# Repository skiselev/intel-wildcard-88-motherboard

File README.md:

# Intel Wildcard 88 Motherboard
An IBM PC/XT compatible motherboard utilizing the [Intel Wildcard 88](documentation/Wildcard%2088%20Datasheet.pdf) module

## Intel Wildcard 88
The Intel Wildcard 88 module was announced by Intel in August 1988. In early 1990's Intel sold Wildcard 88 line to the Canadian [Megatel Computer Corporation](https://web.archive.org/web/20060613014211/http://www.megatel.com/). Here is their [Wildcard 88 page](https://web.archive.org/web/20060615183926/http://megatel.com/html/embedded/control/ov_cwm.htm).

### Specifications of Wildcard 88 module
* The size is about 2" x 4" (50.8mm x 101.6mm)
* Intel 80C88A CPU - 4.77 MHz, 7.15 MHz turbo mode, and 9.54 MHz (Wildcard-88-10N only)
* Custom ASIC implementing functionality of most 82xx ICs (8259 PIC, 8254 PIT, 8237 DMA, 8255 PPI, 8284 clock generator, 8288 bus controller) and glue logic found on an XT motherboard. The ASIC seems actually be the [Faraday FE2010 or FE2010A (for Wildcard-88-10N)](https://github.com/skiselev/micro_8088/blob/master/Documentation/Faraday-XT_Controller-FE2010A.md) chipset
* Half a dozen of 74ALS244 buffers, 74ALS245 transceivers, and 74ALS373 latches to buffer the signals going out of the module.
* Socket for the ROM BIOS. 8 KiB (2764 type), 16 KiB (27C128 type), and 32 KiB (27C256 type) EPROMs are supported.
* Socket for the Intel 8087 floating point co-processor (FPU). Available on the 'N' models only.
* 68-pin SIMM edge connector to connect to the system board. The connector contains all signals found on an XT bus (8-bit ISA), signals required to interface to DRAM (CAS, RAS0 - RAS2, /DRAM, MUX), signals for XT keyboard, speaker output, external reset and video configuration inputs (on 'N' models only)

The Intel Wildcard 88 module was used in several XT compatible computers, for example in the [Leading Edge Model D](https://en.wikipedia.org/wiki/Leading_Edge_Model_D) computers (made by Daewoo). One of more unusual applications - it was used as a control module for the [Nikon NASA F4](https://en.wikipedia.org/wiki/Nikon_NASA_F4) camera, one of the first digital cameras that flew on several Space Shuttle missions.

## The Motherboard

### Overview
Most of the XT computer functionality is implemented on the Wildcard 88 module. The motherboard adds memory, ISA slots, and AT2XT keyboard converter, so that the motherboard can be used with a more modern PS/2 keyboard. It is designed to be as small as possible - the board size is 4.6" x 6.5", but yet functional enough to be used as a generic XT motherboard.

### Specifications
Here are motherboard specifications and ideas behind them:

* 5 ISA slots. Number of slots it tradeoff between board size and extensibility. 5 slots should be enough (the same number as on the original IBM PC motherboard), assuming the slots will be used for the following cards:
  1. Display card
  2. Floppy disk controller card
  3. Hard drive controller card, e.g. XT-IDE or XT-CF-Lite
  4. Audio card
  5. Available for other extension cards (e.g. network).
* The system memory is implemented using single 1 MiB (1 Mbit x 8) SIMM-30 module. The motherboard memory support circuit includes three 74F157 multiplexers, that are used to generate DRAM row / column addresses, a 74F245 buffer for the data bus, and a 74F27 NOR gate used to generate a single /RAS signal from RAS0 - RAS2 signals supplied by the Wildcard 88, and to invert CAS signal. Two otherwise available multiplexers are used to buffer and delay /MEMW signal to memory.
* The motherboard provides PS/2 compatible Mini-DIN keyboard connector.
   * The Wildcard 88 module provides an XT compatible keyboard interface.
   * The motherboard includes an AT2XT keyboard converter, implemented using a PIC12F629 microcontroller.
* Power supply: Motherboard is powered using a 8-pin connector, with 5V, 12V, and -12V voltages. Motherboard includes an LM7905 power regulator is used to convert -12V to -5V. Four diagnostic LEDs are provided on the motherboard to indicate voltage on each power rail. An additional 5V connector on the motherboard can be used to connect power to 3.5" floppy drive.
* The motherboard includes a 12 mm speaker, and a header for connecting an external speaker.
* Jumpers, switches, and connectors:
  * Reset switch - a 6 mm tactile button
  * P5 - Reset header for an external reset switch
  * P6 - Power LED
  * JP1 - VID0 - Video configuration jumper (mono / color)
  * JP2 - AT2XT keyboard converter configuration. Currently, if installed, the jumper configures firmware to pass 0xE0 scan code to the system. This is useful for international keyboards.

### Schematic and PCB Layout

* [Schematic - Version 1.0](KiCad/Wildcard%2088%20Motherboard%20-%20Schematic%20-%201.0.pdf)
* [PCB Layout - Version 1.0](KiCad/Wildcard%2088%20Motherboard%20-%20Board%20-%201.0.pdf)
* [KiCad design files](KiCad/)

### Bill of Materials

* [Wildcard 88 Motherboard project on Mouser](https://www.mouser.com/Tools/Project/Share?AccessID=80f9c13de3): Order most of the components
* [Wildcard 88 Motherboard project on OSHPark](https://oshpark.com/shared_projects/J2usAv54): Order the Wildcard 88 Motherboard PCB

Component type     | Reference | Description                                   | Quantity | Possible sources and notes 
------------------ | --------- | --------------------------------------------- | -------- | --------------------------
PCB                |           | Wildcard 88 Motherboard PCB                   | 1        | Order from a PCB manufacturer of your choice using provided [Gerber](gerber/) or [KiCad](KiCad/WildcardXT.kicad_pcb) files.
Connector          | BUS1 - BUS5 | 62 pin card edge connector, ISA             | 5        | Mouser [571-6-5530843-5](https://www.mouser.com/ProductDetail/571-6-5530843-5), [571-7-5530843-0](https://www.mouser.com/ProductDetail/571-7-5530843-0), [571-5645235-1](https://www.mouser.com/ProductDetail/571-5645235-1)
Capacitor          | C1 - C9   | 0.1uF ceramic capacitor, 5.08 mm lead spacing | 9        | Mouser [810-FG28X7R1H104KNT6](https://www.mouser.com/ProductDetail/810-FG28X7R1H104KNT6)
Capacitor          | C10       | 0.01uF ceramic capacitor, 5.08 mm lead spacing | 1       | Mouser [810-FG28X7R1H103KNT6](https://www.mouser.com/ProductDetail/810-FG28X7R1H103KNT6)
Capacitor          | C11 - C27 | 10uF ceramic or tantalum capacitor, 5.08 mm lead spacing | 17| Mouser [810-FG28X5R1E106MR06](https://www.mouser.com/ProductDetail/810-FG28X5R1E106MR06)
Diode              | D1        | 1N4148                                        | 1        | Mouser [512-1N4148TA](https://www.mouser.com/ProductDetail/512-1N4148TA), [512-1N4148](https://www.mouser.com/ProductDetail/512-1N4148)
LED                | D2-D5     | 3 mm LED, various colors                      | 4        | Mouser [593-VAOL-3LAE2](https://www.mouser.com/ProductDetail/593-VAOL-3LAE2) (Red), [593-VAOL-3GCE4](https://www.mouser.com/ProductDetail/593-VAOL-3GCE4) (Yellow), [593-VAOL-3MDE2](https://www.mouser.com/ProductDetail/593-VAOL-3MDE2) (Green), [593-VAOL-3LSBY2](https://www.mouser.com/ProductDetail/593-VAOL-3LSBY2) (Blue)
Pin Header         | JP1, JP2, P5, P6 | 1x2 pin header                         | 4        | Mouser [649-68002-102HLF](https://www.mouser.com/ProductDetail/649-68002-102HLF)
Connector          | P1        | 8 pin connector with friction lock            | 1        | Mouser [571-6404568](https://www.mouser.com/ProductDetail/571-6404568)
Connector          | P2        | 6 pin Mini DIN connector                      | 1        | Mouser [806-KMDGX-6S-BS](https://www.mouser.com/ProductDetail/806-KMDGX-6S-BS)
Pin Header         | P3        | 1x4 pin header                                | 1        | Mouser [649-68002-204HLF](https://www.mouser.com/ProductDetail/649-68002-204HLF)
Connector          | P4        | 2 pin connector with friction lock            | 1        | Mouser [571-6404562](https://www.mouser.com/ProductDetail/571-6404562)
Transistor         | Q1        | PN2222A                                       | 1        | Mouser [512-PN2222ATA](https://www.mouser.com/ProductDetail/512-PN2222ATA)
Resistor           | R1        | 1k resistor                                   | 1        | Mouser [603-MFR-25FRF521K](https://www.mouser.com/ProductDetail/603-MFR-25FRF521K)
Resistor           | R2 - R4   | 470 ohm resistor                              | 3        | Mouser [603-MFR-25FRF52-470R](https://www.mouser.com/ProductDetail/603-MFR-25FRF52-470R)
Resistor           | R4, R5    | 1.5k resistor                                 | 2        | Mouser [603-MFR-25FRF521K5](https://www.mouser.com/ProductDetail/603-MFR-25FRF521K5)
Resistor Array     | RR1, RR2  | 33 ohm resistor array, DIP-14                 | 2        | Mouser [652-4114R-1LF-33](https://www.mouser.com/ProductDetail/652-4114R-1LF-33), or use 14 discrete resistors [603-MFR-25FRF52-33R](https://www.mouser.com/ProductDetail/603-MFR-25FRF52-33R)
Resistor Array     | RR3, RR4  | 4.7k resistor array, SIP-9                    | 2        | Mouser [652-4609X-1LF-4.7K](https://www.mouser.com/ProductDetail/652-4609X-1LF-4.7K), [858-L091S472LF](https://www.mouser.com/ProductDetail/858-L091S472LF), [652-4309R-1LF-4.7K](https://www.mouser.com/ProductDetail/652-4309R-1LF-4.7K)
Speaker            | SP1       | 12 mm speaker                                 | 1        | Mouser [665-AT-1224TWTR](https://www.mouser.com/ProductDetail/665-AT-1224TWTR)
Button             | SW1       | 6 mm tactile button                           | 1        | Mouser [653-B3F-1000](https://www.mouser.com/ProductDetail/653-B3F-1000)
Module             | U1        | Intel Wildcard 88 Module                      | 1        | eBay
Module             | U2        | SIMM-30 RAM, 1 Mbit x 8                       | 1        | eBay
Integrated Circuit | U3        | PIC12C629                                     | 1        | Mouser [579-PIC12F629IP](https://www.mouser.com/ProductDetail/579-PIC12F629IP), [579-PIC12F629-E/P](https://www.mouser.com/ProductDetail/579-PIC12F629-E-P)
Integrated Circuit | U4        | 74ALS245                                      | 1        | Mouser [595-SN74F245N](https://www.mouser.com/ProductDetail/595-SN74F245N), [595-SN74F245NE4](https://www.mouser.com/ProductDetail/595-SN74F245NE4) [595-SN74ALS245AN](https://www.mouser.com/ProductDetail/595-SN74ALS245AN), [595-SN74ACT245N](https://www.mouser.com/ProductDetail/595-SN74ACT245N), [595-CD74ACT245E](https://www.mouser.com/ProductDetail/595-CD74ACT245E)
Integrated Circuit | U5 - U7   | 74ALS158                                      | 3        | Mouser [595-SN74F157AN](https://www.mouser.com/ProductDetail/595-SN74F157AN), [595-SN74ALS157AN](https://www.mouser.com/ProductDetail/595-SN74ALS157AN), [595-CD74ACT157E](https://www.mouser.com/ProductDetail/595-CD74ACT157E)
Integrated Circuit | U8        | 74ALS27                                       | 1        | Mouser [595-SN74F27N](https://www.mouser.com/ProductDetail/595-SN74F27N), [595-SN74ALS27AN](https://www.mouser.com/ProductDetail/595-SN74ALS27AN)
Integrated Circuit | U9        | LM7905                                        | 1        | Mouser [863-MC7905CTG](https://www.mouser.com/ProductDetail/863-MC7905CTG)
Socket             | U1        | 68 pin SIMM socket, vertical                  | 1        | Make from a 72 pin socket Mouser [571-5822021-4](https://www.mouser.com/ProductDetail/571-5822021-4)
Socket             | U2        | 30 pin SIMM socket, vertical                  | 1        | eBay
Socket             | U3        | 8 pin DIP socket                              | 1        | Mouser [517-4808-3000-CP](https://www.mouser.com/ProductDetail/517-4808-3000-CP)
Socket             | U4        | 20 pin DIP socket                             | 1        | Mouser [517-4820-3000-CP](https://www.mouser.com/ProductDetail/517-4820-3000-CP)
Socket             | U5 - U7   | 16 pin DIP socket                             | 3        | Mouser [517-4816-3000-CP](https://www.mouser.com/ProductDetail/517-4816-3000-CP)
Socket             | U8        | 14 pin DIP socket                             | 1        | Mouser [517-4814-3000-CP](https://www.mouser.com/ProductDetail/517-4814-3000-CP)

## Software

### BIOS

The BIOS binary files from The Leading Edge - Model D are provided in the [software](software/) directory of this repository.

Since the Wildcard 88 module uses [Faraday FE2010 or FE1020A chipsets](https://github.com/skiselev/micro_8088/blob/master/Documentation/Faraday-XT_Controller-FE2010A.md), the [8088 BIOS](https://github.com/skiselev/8088_bios) configured for these chipsets (e.g., Micro 8088 configuration) can be used instead. Note that the Wildcard 88 module uses an EPROM instead of a Flash ROM, therefore the BIOS configuration utility will not work. The BIOS configuration needs to be edited prior to programming the EPROM.

### AT2XT Firmware

The Wildcard 88 Motherboard integrates an AT2XT keyboard converter, implemented using PIC12F629 (U3). The firmware for this microcontroller is availabe from the [minuszerodegrees.net](http://minuszerodegrees.net/at2xtkb/XTATKEY_094.zip) and the [Vintage Computer Federation AT2XT page](https://forum.vcfed.org/index.php?threads/at2xt-keyboard-converter.26861/page-4#post-1242916). The HEX file with the firmware can be extracted from XTATKEY_094.zip.

## Red Tape

### Licensing

Intel Wildcard 88 Motherboard is an open source hardware project. The hardware design itself, including schematic and PCB layout design files are licensed under the strongly-reciprocal variant of [CERN Open Hardware Licence version 2](license-cern_ohl_s_v2.txt). Documentation, including this file, is licensed under the [Creative Commons Attribution-ShareAlike 4.0 International License](license-cc-by-sa-4.0.txt).

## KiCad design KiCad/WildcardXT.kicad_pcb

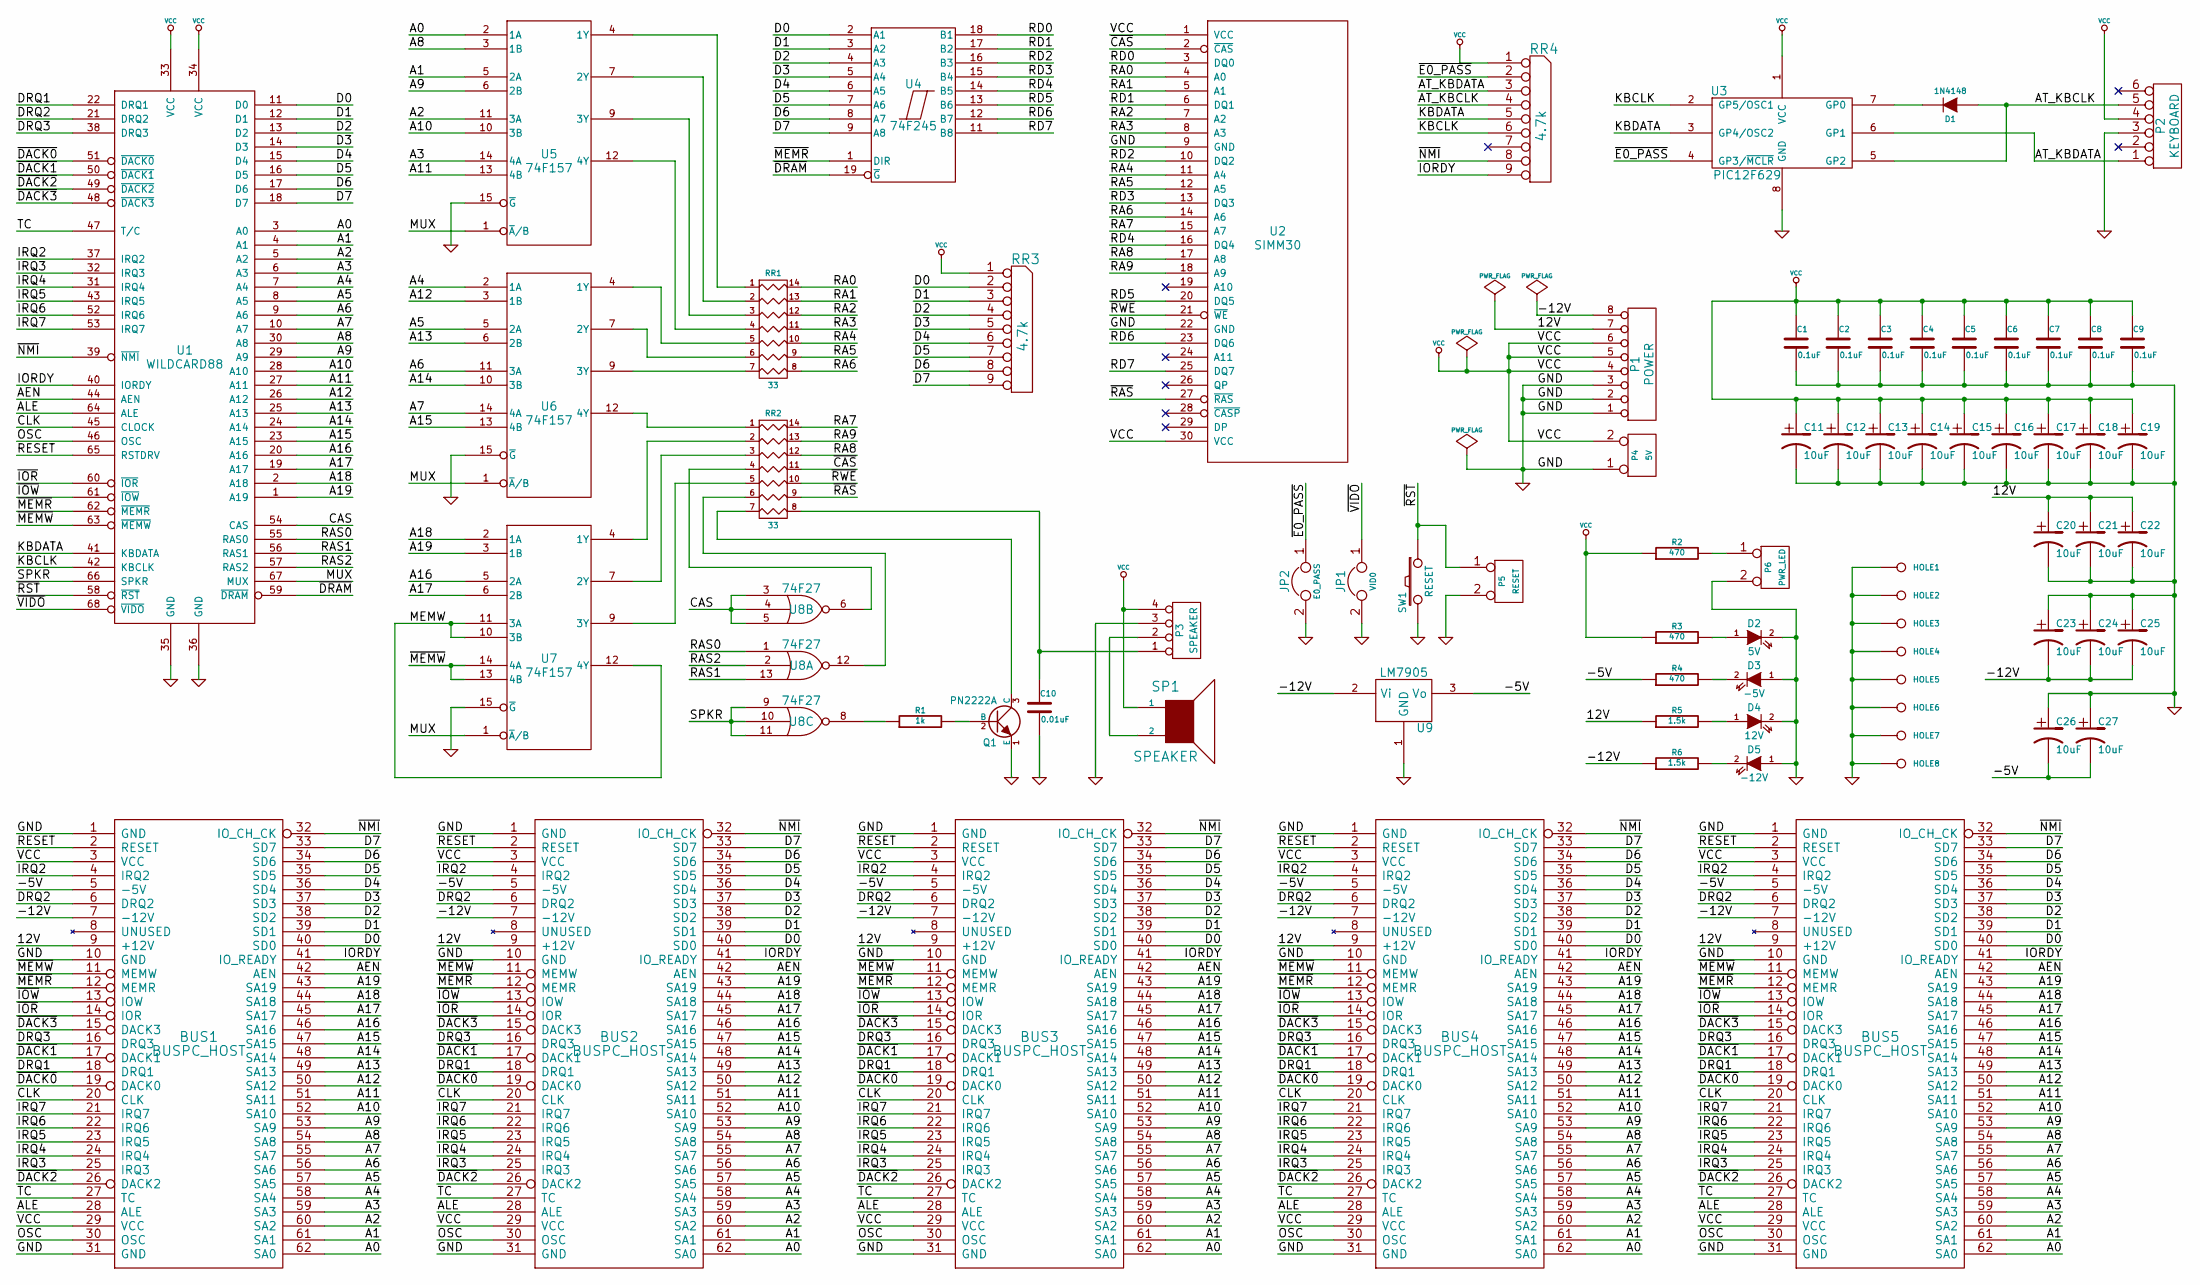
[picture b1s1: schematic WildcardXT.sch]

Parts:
BUS1, BUS2, BUS3, BUS4, BUS5: BUSPC_HOST
C1, C2, C3, C4, C5, C6, C7, C8, C9: 0.1uF
C10: 0.01uF
C11, C12, C13, C14, C15, C16, C17, C18, C19, C20, C21, C22, C23, C24, C25, C26, C27: 10uF
D1: 1N4148
D2: 5V
D3: -5V
D4: 12V
D5: -12V
HOLE1, HOLE2, HOLE3, HOLE4, HOLE5, HOLE6, HOLE7, HOLE8: CONN_1
JP1: VID0
JP2: E0_PASS
P1: POWER
P2: KEYBOARD
P3: SPEAKER
P4: 5V
P5: RESET
P6: PWR_LED
Q1: PN2222A
R1: 1k
R2, R3, R4: 470
R5, R6: 1.5k
RR1, RR2: 33
RR3, RR4: 4.7k
SP1: SPEAKER
SW1: RESET
U1: WILDCARD88
U2: SIMM30
U3: PIC12F629
U4: 74F245
U5, U6, U7: 74F157
U8: 74F27
U9: LM7905

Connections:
/12V: BUS1.9 (+12V), BUS2.9 (+12V), BUS3.9 (+12V), BUS4.9 (+12V), BUS5.9 (+12V), C20.1, C21.1, C22.1, P1.7, R5.1
/-5V: BUS1.5 (-5V), BUS2.5 (-5V), BUS3.5 (-5V), BUS4.5 (-5V), BUS5.5 (-5V), C26.2, C27.2, R4.1, U9.3 (Vo)
/-12V: BUS1.7 (-12V), BUS2.7 (-12V), BUS3.7 (-12V), BUS4.7 (-12V), BUS5.7 (-12V), C23.2, C24.2, C25.2, P1.8, R6.1, U9.2 (Vi)
/A0: BUS1.62 (SA0), BUS2.62 (SA0), BUS3.62 (SA0), BUS4.62 (SA0), BUS5.62 (SA0), U1.3 (A0), U5.2 (1A)
/A1: BUS1.61 (SA1), BUS2.61 (SA1), BUS3.61 (SA1), BUS4.61 (SA1), BUS5.61 (SA1), U1.4 (A1), U5.5 (2A)
/A2: BUS1.60 (SA2), BUS2.60 (SA2), BUS3.60 (SA2), BUS4.60 (SA2), BUS5.60 (SA2), U1.5 (A2), U5.11 (3A)
/A3: BUS1.59 (SA3), BUS2.59 (SA3), BUS3.59 (SA3), BUS4.59 (SA3), BUS5.59 (SA3), U1.6 (A3), U5.14 (4A)
/A4: BUS1.58 (SA4), BUS2.58 (SA4), BUS3.58 (SA4), BUS4.58 (SA4), BUS5.58 (SA4), U1.7 (A4), U6.2 (1A)
/A5: BUS1.57 (SA5), BUS2.57 (SA5), BUS3.57 (SA5), BUS4.57 (SA5), BUS5.57 (SA5), U1.8 (A5), U6.5 (2A)
/A6: BUS1.56 (SA6), BUS2.56 (SA6), BUS3.56 (SA6), BUS4.56 (SA6), BUS5.56 (SA6), U1.9 (A6), U6.11 (3A)
/A7: BUS1.55 (SA7), BUS2.55 (SA7), BUS3.55 (SA7), BUS4.55 (SA7), BUS5.55 (SA7), U1.10 (A7), U6.14 (4A)
/A8: BUS1.54 (SA8), BUS2.54 (SA8), BUS3.54 (SA8), BUS4.54 (SA8), BUS5.54 (SA8), U1.30 (A8), U5.3 (1B)
/A9: BUS1.53 (SA9), BUS2.53 (SA9), BUS3.53 (SA9), BUS4.53 (SA9), BUS5.53 (SA9), U1.29 (A9), U5.6 (2B)
/A10: BUS1.52 (SA10), BUS2.52 (SA10), BUS3.52 (SA10), BUS4.52 (SA10), BUS5.52 (SA10), U1.28 (A10), U5.10 (3B)
/A11: BUS1.51 (SA11), BUS2.51 (SA11), BUS3.51 (SA11), BUS4.51 (SA11), BUS5.51 (SA11), U1.27 (A11), U5.13 (4B)
/A12: BUS1.50 (SA12), BUS2.50 (SA12), BUS3.50 (SA12), BUS4.50 (SA12), BUS5.50 (SA12), U1.26 (A12), U6.3 (1B)
/A13: BUS1.49 (SA13), BUS2.49 (SA13), BUS3.49 (SA13), BUS4.49 (SA13), BUS5.49 (SA13), U1.25 (A13), U6.6 (2B)
/A14: BUS1.48 (SA14), BUS2.48 (SA14), BUS3.48 (SA14), BUS4.48 (SA14), BUS5.48 (SA14), U1.24 (A14), U6.10 (3B)
/A15: BUS1.47 (SA15), BUS2.47 (SA15), BUS3.47 (SA15), BUS4.47 (SA15), BUS5.47 (SA15), U1.23 (A15), U6.13 (4B)
/A16: BUS1.46 (SA16), BUS2.46 (SA16), BUS3.46 (SA16), BUS4.46 (SA16), BUS5.46 (SA16), U1.20 (A16), U7.5 (2A)
/A17: BUS1.45 (SA17), BUS2.45 (SA17), BUS3.45 (SA17), BUS4.45 (SA17), BUS5.45 (SA17), U1.19 (A17), U7.6 (2B)
/A18: BUS1.44 (SA18), BUS2.44 (SA18), BUS3.44 (SA18), BUS4.44 (SA18), BUS5.44 (SA18), U1.2 (A18), U7.2 (1A)
/A19: BUS1.43 (SA19), BUS2.43 (SA19), BUS3.43 (SA19), BUS4.43 (SA19), BUS5.43 (SA19), U1.1 (A19), U7.3 (1B)
/AEN: BUS1.42 (AEN), BUS2.42 (AEN), BUS3.42 (AEN), BUS4.42 (AEN), BUS5.42 (AEN), U1.44 (AEN)
/ALE: BUS1.28 (ALE), BUS2.28 (ALE), BUS3.28 (ALE), BUS4.28 (ALE), BUS5.28 (ALE), U1.64 (ALE)
/AT_KBCLK: D1.1 (A), P2.5, RR4.4, U3.5 (GP2)
/AT_KBDATA: P2.1, RR4.3, U3.6 (GP1)
/CAS: U1.54 (CAS), U8.3, U8.4, U8.5
/CLK: BUS1.20 (CLK), BUS2.20 (CLK), BUS3.20 (CLK), BUS4.20 (CLK), BUS5.20 (CLK), U1.45 (CLOCK)
/D0: BUS1.40 (SD0), BUS2.40 (SD0), BUS3.40 (SD0), BUS4.40 (SD0), BUS5.40 (SD0), RR3.2, U1.11 (D0), U4.2 (A1)
/D1: BUS1.39 (SD1), BUS2.39 (SD1), BUS3.39 (SD1), BUS4.39 (SD1), BUS5.39 (SD1), RR3.3, U1.12 (D1), U4.3 (A2)
/D2: BUS1.38 (SD2), BUS2.38 (SD2), BUS3.38 (SD2), BUS4.38 (SD2), BUS5.38 (SD2), RR3.4, U1.13 (D2), U4.4 (A3)
/D3: BUS1.37 (SD3), BUS2.37 (SD3), BUS3.37 (SD3), BUS4.37 (SD3), BUS5.37 (SD3), RR3.5, U1.14 (D3), U4.5 (A4)
/D4: BUS1.36 (SD4), BUS2.36 (SD4), BUS3.36 (SD4), BUS4.36 (SD4), BUS5.36 (SD4), RR3.6, U1.15 (D4), U4.6 (A5)
/D5: BUS1.35 (SD5), BUS2.35 (SD5), BUS3.35 (SD5), BUS4.35 (SD5), BUS5.35 (SD5), RR3.7, U1.16 (D5), U4.7 (A6)
/D6: BUS1.34 (SD6), BUS2.34 (SD6), BUS3.34 (SD6), BUS4.34 (SD6), BUS5.34 (SD6), RR3.8, U1.17 (D6), U4.8 (A7)
/D7: BUS1.33 (SD7), BUS2.33 (SD7), BUS3.33 (SD7), BUS4.33 (SD7), BUS5.33 (SD7), RR3.9, U1.18 (D7), U4.9 (A8)
/DRQ1: BUS1.18 (DRQ1), BUS2.18 (DRQ1), BUS3.18 (DRQ1), BUS4.18 (DRQ1), BUS5.18 (DRQ1), U1.22 (DRQ1)
/DRQ2: BUS1.6 (DRQ2), BUS2.6 (DRQ2), BUS3.6 (DRQ2), BUS4.6 (DRQ2), BUS5.6 (DRQ2), U1.21 (DRQ2)
/DRQ3: BUS1.16 (DRQ3), BUS2.16 (DRQ3), BUS3.16 (DRQ3), BUS4.16 (DRQ3), BUS5.16 (DRQ3), U1.38 (DRQ3)
/IORDY: BUS1.41 (IO_READY), BUS2.41 (IO_READY), BUS3.41 (IO_READY), BUS4.41 (IO_READY), BUS5.41 (IO_READY), RR4.9, U1.40 (IORDY)
/IRQ2: BUS1.4 (IRQ2), BUS2.4 (IRQ2), BUS3.4 (IRQ2), BUS4.4 (IRQ2), BUS5.4 (IRQ2), U1.37 (IRQ2)
/IRQ3: BUS1.25 (IRQ3), BUS2.25 (IRQ3), BUS3.25 (IRQ3), BUS4.25 (IRQ3), BUS5.25 (IRQ3), U1.32 (IRQ3)
/IRQ4: BUS1.24 (IRQ4), BUS2.24 (IRQ4), BUS3.24 (IRQ4), BUS4.24 (IRQ4), BUS5.24 (IRQ4), U1.31 (IRQ4)
/IRQ5: BUS1.23 (IRQ5), BUS2.23 (IRQ5), BUS3.23 (IRQ5), BUS4.23 (IRQ5), BUS5.23 (IRQ5), U1.43 (IRQ5)
/IRQ6: BUS1.22 (IRQ6), BUS2.22 (IRQ6), BUS3.22 (IRQ6), BUS4.22 (IRQ6), BUS5.22 (IRQ6), U1.52 (IRQ6)
/IRQ7: BUS1.21 (IRQ7), BUS2.21 (IRQ7), BUS3.21 (IRQ7), BUS4.21 (IRQ7), BUS5.21 (IRQ7), U1.53 (IRQ7)
/KBCLK: RR4.6, U1.42 (KBCLK), U3.2 (GP5/OSC1)
/KBDATA: RR4.5, U1.41 (KBDATA), U3.3 (GP4/OSC2)
/MEMW: U7.10 (3B), U7.11 (3A), U7.12 (4Y)
/MUX: U1.67 (MUX), U5.1 (~A~/B), U6.1 (~A~/B), U7.1 (~A~/B)
/OSC: BUS1.30 (OSC), BUS2.30 (OSC), BUS3.30 (OSC), BUS4.30 (OSC), BUS5.30 (OSC), U1.46 (OSC)
/RA0: RR1.14 (R3), U2.4 (A0)
/RA1: RR1.13 (R4), U2.5 (A1)
/RA2: RR1.12 (R5), U2.7 (A2)
/RA3: RR1.11 (R6), U2.8 (A3)
/RA4: RR1.10 (R7), U2.11 (A4)
/RA5: RR1.9 (R8), U2.12 (A5)
/RA6: RR1.8, U2.14 (A6)
/RA7: RR2.14 (R3), U2.15 (A7)
/RA8: RR2.12 (R5), U2.17 (A8)
/RA9: RR2.13 (R4), U2.18 (A9)
/RAS0: U1.55 (RAS0), U8.1
/RAS1: U1.56 (RAS1), U8.13
/RAS2: U1.57 (RAS2), U8.2
/RD0: U2.3 (DQ0), U4.18 (B1)
/RD1: U2.6 (DQ1), U4.17 (B2)
/RD2: U2.10 (DQ2), U4.16 (B3)
/RD3: U2.13 (DQ3), U4.15 (B4)
/RD4: U2.16 (DQ4), U4.14 (B5)
/RD5: U2.20 (DQ5), U4.13 (B6)
/RD6: U2.23 (DQ6), U4.12 (B7)
/RD7: U2.25 (DQ7), U4.11 (B8)
/RESET: BUS1.2 (RESET), BUS2.2 (RESET), BUS3.2 (RESET), BUS4.2 (RESET), BUS5.2 (RESET), U1.65 (RSTDRV)
/SPKR: U1.66 (SPKR), U8.9, U8.10, U8.11
/TC: BUS1.27 (TC), BUS2.27 (TC), BUS3.27 (TC), BUS4.27 (TC), BUS5.27 (TC), U1.47 (T/C)
/~CAS: RR2.11 (R6), U2.2 (~CAS)
/~DACK0: BUS1.19 (DACK0), BUS2.19 (DACK0), BUS3.19 (DACK0), BUS4.19 (DACK0), BUS5.19 (DACK0), U1.51 (~DACK0)
/~DACK1: BUS1.17 (DACK1), BUS2.17 (DACK1), BUS3.17 (DACK1), BUS4.17 (DACK1), BUS5.17 (DACK1), U1.50 (~DACK1)
/~DACK2: BUS1.26 (DACK2), BUS2.26 (DACK2), BUS3.26 (DACK2), BUS4.26 (DACK2), BUS5.26 (DACK2), U1.49 (~DACK2)
/~DACK3: BUS1.15 (DACK3), BUS2.15 (DACK3), BUS3.15 (DACK3), BUS4.15 (DACK3), BUS5.15 (DACK3), U1.48 (~DACK3)
/~DRAM: U1.59 (~DRAM), U4.19 (~G)
/~E0_PASS: JP2.1, RR4.2, U3.4 (GP3/~MCLR)
/~IOR: BUS1.14 (IOR), BUS2.14 (IOR), BUS3.14 (IOR), BUS4.14 (IOR), BUS5.14 (IOR), U1.60 (~IOR)
/~IOW: BUS1.13 (IOW), BUS2.13 (IOW), BUS3.13 (IOW), BUS4.13 (IOW), BUS5.13 (IOW), U1.61 (~IOW)
/~MEMR: BUS1.12 (MEMR), BUS2.12 (MEMR), BUS3.12 (MEMR), BUS4.12 (MEMR), BUS5.12 (MEMR), U1.62 (~MEMR), U4.1 (DIR)
/~MEMW: BUS1.11 (MEMW), BUS2.11 (MEMW), BUS3.11 (MEMW), BUS4.11 (MEMW), BUS5.11 (MEMW), U1.63 (~MEMW), U7.13 (4B), U7.14 (4A)
/~NMI: BUS1.32 (IO_CH_CK), BUS2.32 (IO_CH_CK), BUS3.32 (IO_CH_CK), BUS4.32 (IO_CH_CK), BUS5.32 (IO_CH_CK), RR4.8, U1.39 (~NMI)
/~RAS: RR2.9 (R8), U2.27 (~RAS)
/~RST: P5.1, SW1.1, U1.58 (~RST)
/~RWE: RR2.10 (R7), U2.21 (~WE)
/~VIDO: JP1.1, U1.68 (~VIDO)
GND: BUS1.1 (GND), BUS1.10 (GND), BUS1.31 (GND), BUS2.1 (GND), BUS2.10 (GND), BUS2.31 (GND), BUS3.1 (GND), BUS3.10 (GND), BUS3.31 (GND), BUS4.1 (GND), BUS4.10 (GND), BUS4.31 (GND), BUS5.1 (GND), BUS5.10 (GND), BUS5.31 (GND), C1.2, C2.2, C3.2, C4.2, C5.2, C6.2, C7.2, C8.2, C9.2, C10.2, C11.2, C12.2, C13.2, C14.2, C15.2, C16.2, C17.2, C18.2, C19.2, C20.2, C21.2, C22.2, C23.1, C24.1, C25.1, C26.1, C27.1, D2.2 (K), D3.1 (A), D4.2 (K), D5.1 (A), HOLE1.1, HOLE2.1, HOLE3.1, HOLE4.1, HOLE5.1, HOLE6.1, HOLE7.1, HOLE8.1, JP1.2, JP2.2, P1.1, P1.2, P1.3, P2.3, P2.~, P3.3, P4.1, P5.2 (PM), P6.2 (PM), Q1.1 (E), SW1.2, U1.35 (GND), U1.36 (GND), U2.9 (GND), U2.22 (GND), U2.~, U3.8 (GND), U4.10 (GND), U5.8 (GND), U5.15 (~G), U6.8 (GND), U6.15 (~G), U7.8 (GND), U7.15 (~G), U8.7 (GND), U9.1 (GND)
unnamed: RR1.6, U6.7 (2Y)
unnamed: RR2.1, U6.12 (4Y)
unnamed: RR2.3, U7.7 (2Y)
unnamed: RR1.2, U5.7 (2Y)
unnamed: RR1.4, U5.12 (4Y)
unnamed: P3.2, SP1.2
unnamed: R1.1, U8.8
unnamed: RR2.4, U8.6
unnamed: RR2.6, U8.12
unnamed: D2.1 (A), R3.2
unnamed: Q1.2 (B), R1.2
unnamed: P6.1, R2.2
unnamed: RR2.5, U7.9 (3Y)
unnamed: RR1.7, U6.9 (3Y)
unnamed: D4.1 (A), R5.2
unnamed: D3.2 (K), R4.2
unnamed: D5.2 (K), R6.2
unnamed: RR1.1, U5.4 (1Y)
unnamed: RR2.2, U7.4 (1Y)
unnamed: RR1.5, U6.4 (1Y)
unnamed: RR1.3, U5.9 (3Y)
unnamed: D1.2 (K), U3.7 (GP0)
unnamed: Q1.3 (C), RR2.7
unnamed: C10.1, P3.1, RR2.8
VCC: BUS1.3 (VCC), BUS1.29 (VCC), BUS2.3 (VCC), BUS2.29 (VCC), BUS3.3 (VCC), BUS3.29 (VCC), BUS4.3 (VCC), BUS4.29 (VCC), BUS5.3 (VCC), BUS5.29 (VCC), C1.1, C2.1, C3.1, C4.1, C5.1, C6.1, C7.1, C8.1, C9.1, C11.1, C12.1, C13.1, C14.1, C15.1, C16.1, C17.1, C18.1, C19.1, P1.4, P1.5, P1.6, P2.4, P3.4, P4.2 (PM), R2.1, R3.1, RR3.1 (COM), RR4.1 (COM), SP1.1, U1.33 (VCC), U1.34 (VCC), U2.1 (VCC), U2.30 (VCC), U3.1 (VCC), U4.20 (VCC), U5.16 (VCC), U6.16 (VCC), U7.16 (VCC), U8.14 (VCC)

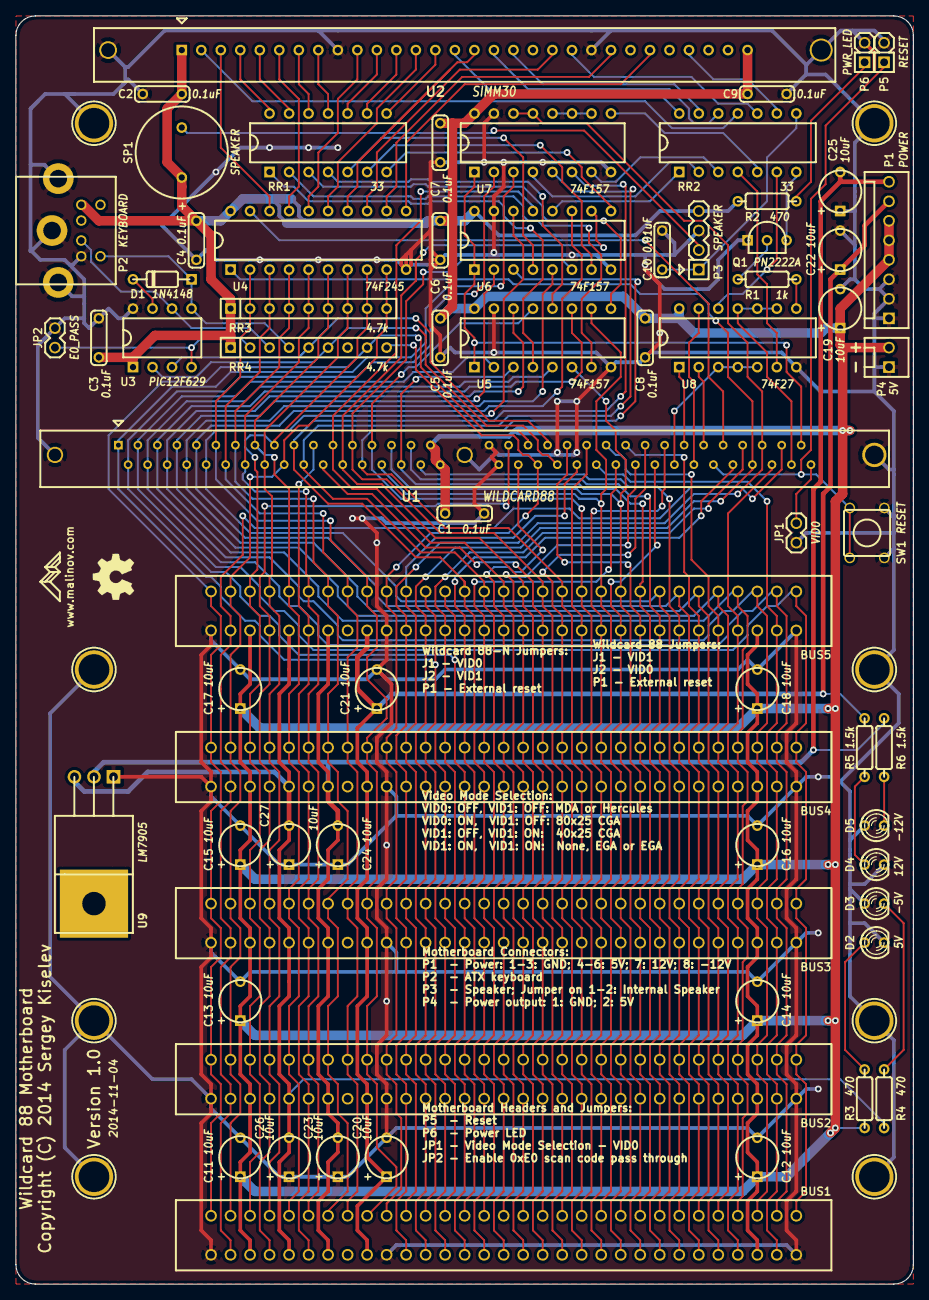
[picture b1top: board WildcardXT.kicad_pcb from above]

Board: 2 copper layers, 116.8 x 165.1 mm, 75 parts (0 on the bottom side), 118 nets.

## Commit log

2025-11-21 Populate README.md
2025-11-21 README: Update links to the documentation and software
2025-11-21 README: Add pictures
2025-11-22 README: Add Mouser links to most of the components
2025-11-22 README: Add the rest of Mouser links to the BoM; Add AT2XT Firmware section
2025-11-22 README: Add link to the Mouser project
2025-11-22 Add Award BIOS from pietja @ VCF
2025-11-22 Add NASA Electronic Still Camera documents

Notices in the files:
KiCad/WildcardXT.kicad_pcb:
Copyright (C) 2014 Sergey Kiselev
